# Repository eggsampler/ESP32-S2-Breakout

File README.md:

# ESP32-S2-Breakout

**May 2021:** New v2 boards [assembled with USB-C connector](https://cdn.discordapp.com/attachments/743434443859034135/847350110374461490/image0.jpg), tested and working well over USB CDC-ACM and DFU programming.

**Feb 2021:** Updated to v2, switched from micro usb to usb-c connector, minor routing changes. PCB ordered, updates to come.

**July 2020:** Board has been [assembled](https://i.imgur.com/Ixv2GHa.jpg), but not fully tested. Currently waiting for ESP-IDF release with full s2 support.

This board is a minimal breakout board for the new ESP32-S2-WROOM module from [Espressif](https://www.espressif.com/). It was designed with a few criteria in mind,

- Breakout as many pins as possible, if not all, from the module
- Be relatively easy for a hobbyist to order & assemble
- Use a minimal amount of components

To that end, a few choices were made,

- Designed in [KiCad](https://kicad.org/) to be accessible to most people
- Use as little active components as possible
  - Note, it is definitely possible to use less than is currently laid out and the design will (slowly) be iterated on towards this.
- Using 0603 (imperial) sized passives
  - Ideally the board would be constructed using solder paste, a stencil and either some form of reflow oven or hot plate (even a [skillet on a stove](https://www.sparkfun.com/tutorials/59) is fine)
- To have the boards cheaply manufactured by most turn-key pcb fab houses,
  - Power traces should be at least 12 mil
  - Signal traces should be at least 8 mil
  - Vias should be 0.3mm drill size with a 0.6mm pad size
- No LGA parts, and ideally no QFN parts

## Initial Design

The initial design was taken from the [ESP32-S2-WROOM & ESP32-S2-WROOM-I Datasheet](https://www.espressif.com/sites/default/files/documentation/esp32-s2-wroom_esp32-s2-wroom-i_datasheet_en.pdf) (v0.5) section *6. Peripheral Schematics* Figure 5.

A few changes were made from this schematic.

- The USB data lines were directed to a USB-C connector
- 22 ohm termination resistors are used on the USB data lines, along with including the 20pF caps
- No 0 resistor was used on the EN reset switch, just tied directly to the EN pin
- A switch was also used on IO0 for the boot mode, instead of a connector/header
- No separate connectors for UART/JTAG, all pins were broken out to 2.54mm/0.1" headers

## Component Selection

### 1. 3v3 Regulator

A regulator which has high efficiencies (ie, low ground/quiescent current) is needed to get the best out of powering the device from higher voltages. The XC6220 has a hysterisis mode called "Green Operation" where the supply current current is much lower when the load current is below 2mA. The v1 of this board will also be a bit of a test for this regulator to see how it handles higher loads for wifi, and lower loads for sleep modes.

### 2. 32.768 KHz Crystal

A few resources were useful when researching crystal and component choices.

1. https://en.wikipedia.org/wiki/Pierce_oscillator
2. http://ww1.microchip.com/downloads/en/AppNotes/00943A.pdf
3. http://www.crystek.com/documents/appnotes/Pierce-GateIntroduction.pdf
4. http://www.st.com/internet/com/TECHNICAL_RESOURCES/TECHNICAL_LITERATURE/APPLICATION_NOTE/CD00221665.pdf

A cheap crystal FC-135 with a max ESR of 70kOhms was used which fits on the KiCad 3215 pad. A few passive values will need to be tested for v1 to determine if they're even necessary.

### 3. Switches / Connectors

The switches and connectors were chosen because they had footprints already in the KiCad library and are relatively accessible from most vendors.

### 4. USB ESD Protection

A USBLC6-2SC6 was chosen for ESD protection of the USB power and data lines. This part was already available in KiCad and at a few distributors. An input capacitor was used fort this part, along with a ferrite bead before the 5v bus.

Another ferrite bead and capacitor was used between the shield and the ground. Probably not strictly necessary.

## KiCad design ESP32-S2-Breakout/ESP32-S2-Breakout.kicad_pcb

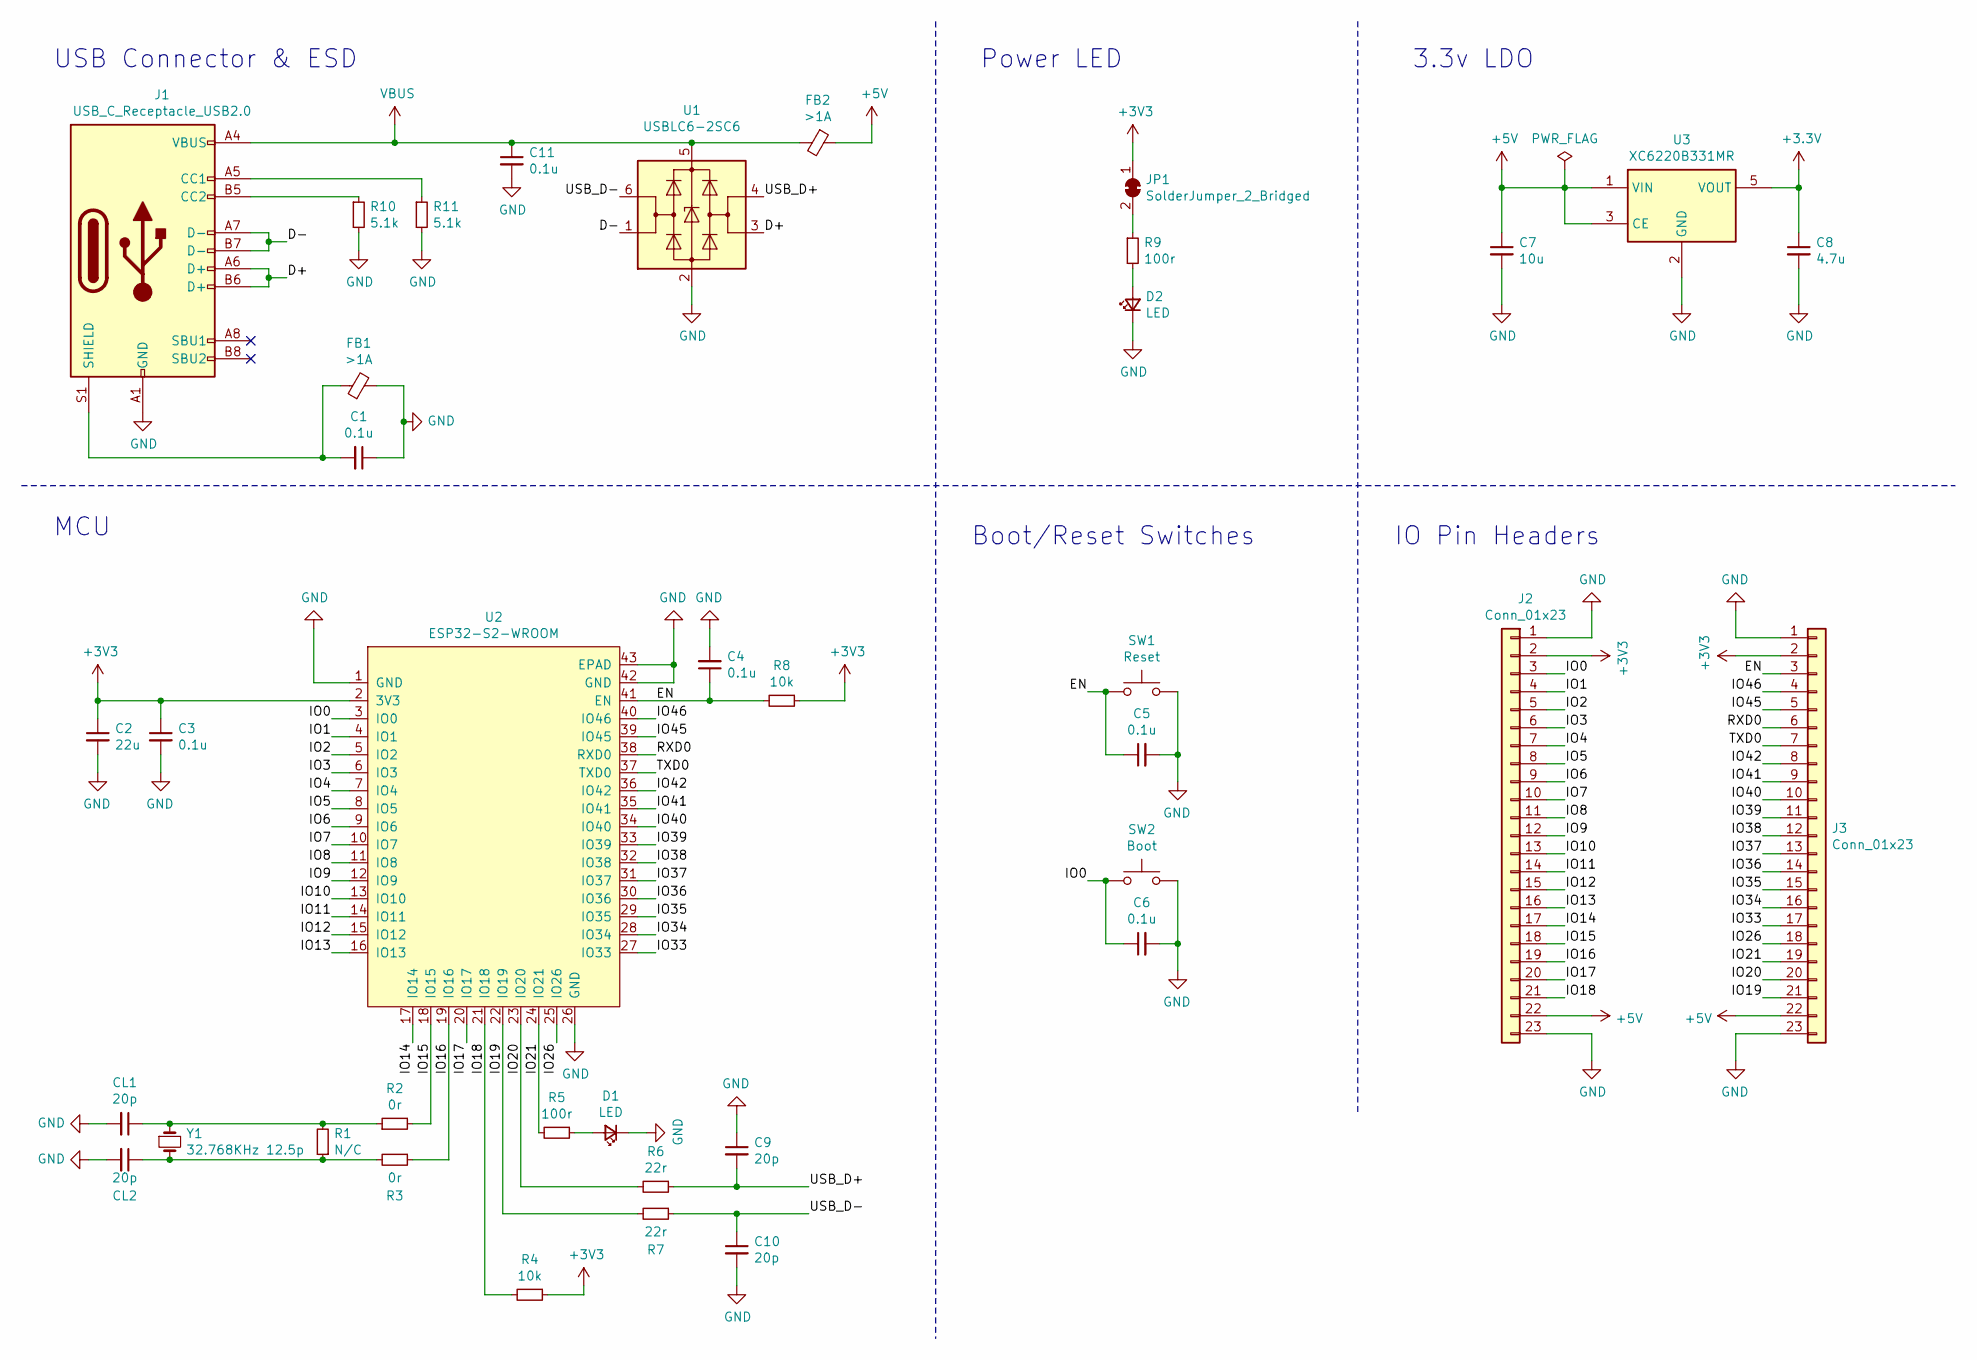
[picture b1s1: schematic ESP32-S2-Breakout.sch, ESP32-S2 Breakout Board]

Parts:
C1, C3, C4, C5, C6, C11: 0.1u; C_0603_1608Metric; LCSC C14663
C2: 22u; C_0603_1608Metric; LCSC C84419
C7: 10u; C_0603_1608Metric; LCSC C90058
C8: 4.7u; C_0603_1608Metric; LCSC C69335
C9, C10: 20p; C_0603_1608Metric; LCSC C1648
CL1, CL2: 20p; C_0603_1608Metric; LCSC C1648
D1: LED; LED_0603_1608Metric; LCSC C205443
D2: LED; LED_0603_1608Metric; LCSC C205445
FB1, FB2: >1A; L_0603_1608Metric; LCSC C24821
J1: USB_C_Receptacle_USB2.0; USB_C_Receptacle_HRO_TYPE-C-31-M-12; LCSC C165948
J2, J3: Conn_01x23; PinHeader_1x23_P2.54mm_Vertical
JP1: SolderJumper_2_Bridged; SolderJumper-2_P1.3mm_Bridged_RoundedPad1.0x1.5mm
R1: N/C; R_0603_1608Metric
R2, R3: 0r; R_0603_1608Metric; LCSC C21189
R4, R8: 10k; R_0603_1608Metric; LCSC C99198
R5, R9: 100r; R_0603_1608Metric; LCSC C22775
R6, R7: 22r; R_0603_1608Metric; LCSC C23345
R10, R11: 5.1k; R_0603_1608Metric; LCSC C163928
SW1: Reset; Alps_SKRK; LCSC C115357
SW2: Boot; Alps_SKRK; LCSC C115357
U1: USBLC6-2SC6; SOT-23-6; LCSC C7519
U2: ESP32-S2-WROOM; LCSC C701327
U3: XC6220B331MR; SOT-23-5; LCSC C86534
Y1: 32.768KHz 12.5p; Crystal_SMD_3215-2Pin_3.2x1.5mm; LCSC C271654

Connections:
+5V: C7.1, FB2.1, J2.22, J3.22, U3.1 (VIN), U3.3 (CE)
/D+: J1.A6 (D+), J1.B6 (D+), U1.3 (I/O2)
/D-: J1.A7 (D-), J1.B7 (D-), U1.1 (I/O1)
/EN: C4.1, C5.1, J3.3, R8.2, SW1.2, U2.41 (EN)
/IO0: C6.1, J2.3, SW2.2, U2.3 (IO0)
/IO1: J2.4, U2.4 (IO1)
/IO2: J2.5, U2.5 (IO2)
/IO3: J2.6, U2.6 (IO3)
/IO4: J2.7, U2.7 (IO4)
/IO5: J2.8, U2.8 (IO5)
/IO6: J2.9, U2.9 (IO6)
/IO7: J2.10, U2.10 (IO7)
/IO8: J2.11, U2.11 (IO8)
/IO9: J2.12, U2.12 (IO9)
/IO10: J2.13, U2.13 (IO10)
/IO11: J2.14, U2.14 (IO11)
/IO12: J2.15, U2.15 (IO12)
/IO13: J2.16, U2.16 (IO13)
/IO14: J2.17, U2.17 (IO14)
/IO15: J2.18, R2.2, U2.18 (IO15)
/IO16: J2.19, R3.1, U2.19 (IO16)
/IO17: J2.20, U2.20 (IO17)
/IO18: J2.21, R4.2, U2.21 (IO18)
/IO19: J3.21, R7.2, U2.22 (IO19)
/IO20: J3.20, R6.2, U2.23 (IO20)
/IO21: J3.19, R5.2, U2.24 (IO21)
/IO26: J3.18, U2.25 (IO26)
/IO33: J3.17, U2.27 (IO33)
/IO34: J3.16, U2.28 (IO34)
/IO35: J3.15, U2.29 (IO35)
/IO36: J3.14, U2.30 (IO36)
/IO37: J3.13, U2.31 (IO37)
/IO38: J3.12, U2.32 (IO38)
/IO39: J3.11, U2.33 (IO39)
/IO40: J3.10, U2.34 (IO40)
/IO41: J3.9, U2.35 (IO41)
/IO42: J3.8, U2.36 (IO42)
/IO45: J3.5, U2.39 (IO45)
/IO46: J3.4, U2.40 (IO46)
/RXD0: J3.6, U2.38 (RXD0)
/TXD0: J3.7, U2.37 (TXD0)
/USB_D+: C9.2, R6.1, U1.4 (I/O2)
/USB_D-: C10.1, R7.1, U1.6 (I/O1)
GND: C1.1, C2.2, C3.2, C4.2, C5.2, C6.2, C7.2, C8.2, C9.1, C10.2, C11.2, CL1.2, CL2.2, D1.1 (K), D2.1 (K), FB1.2, J1.A1 (GND), J1.A12 (GND), J1.B1 (GND), J1.B12 (GND), J2.1, J2.23, J3.1, J3.23, R10.2, R11.2, SW1.1, SW2.1, U1.2 (GND), U2.1 (GND), U2.26 (GND), U2.42 (GND), U2.43 (EPAD), U3.2 (GND)
unnamed: C1.2, FB1.1, J1.S1 (SHIELD)
unnamed: CL1.1, R1.2, R2.1, Y1.1
unnamed: CL2.1, R1.1, R3.2, Y1.2
unnamed: D1.2 (A), R5.1
unnamed: D2.2 (A), R9.2
unnamed: J1.A5 (CC1), R11.1
unnamed: J1.B5 (CC2), R10.1
unnamed: JP1.2 (B), R9.1
VBUS: C11.1, FB2.2, J1.A4 (VBUS), J1.A9 (VBUS), J1.B4 (VBUS), J1.B9 (VBUS), U1.5 (VBUS)

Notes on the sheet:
USB Connector & ESD
Power LED
3.3v LDO
MCU
Boot/Reset Switches
IO Pin Headers

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
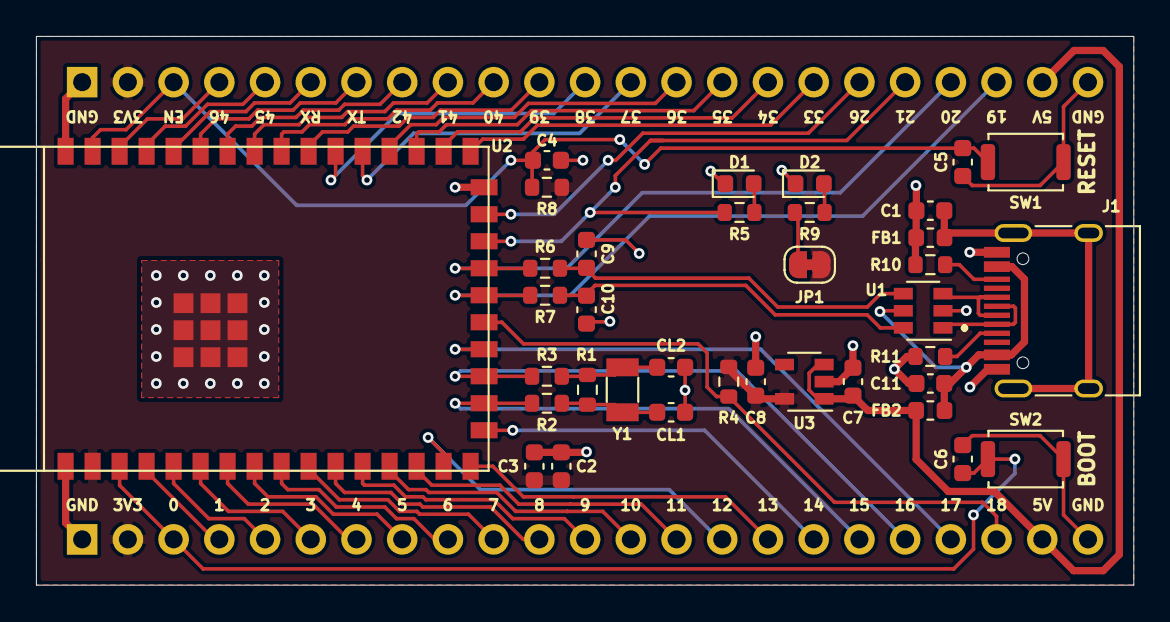
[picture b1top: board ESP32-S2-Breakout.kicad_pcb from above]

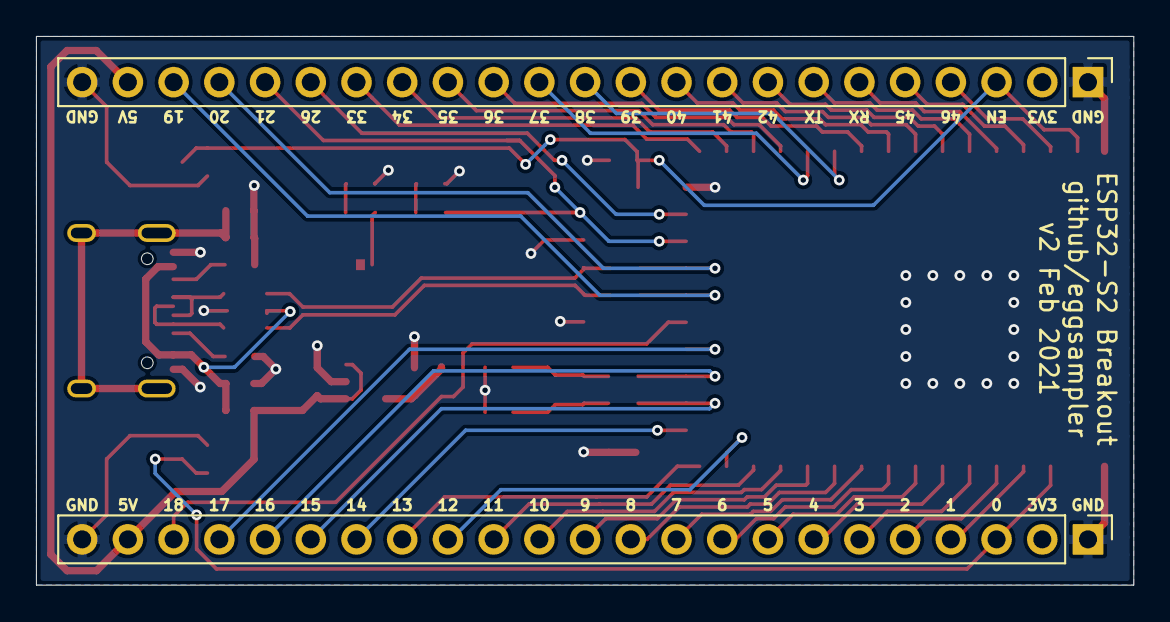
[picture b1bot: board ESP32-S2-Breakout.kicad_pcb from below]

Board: 2 copper layers, 61.0 x 30.5 mm, 38 parts (2 on the bottom side), 54 nets.

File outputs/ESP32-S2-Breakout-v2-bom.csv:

Qty,Reference(s),Value,Footprint,LCSC
6,"C1, C3, C4, C5, C6, C11",0.1u X7R 50V,C_0603_1608Metric,C14663
1,C2,22u X5R 10V,C_0603_1608Metric,C59461
1,C7,10u X5R 16V,C_0603_1608Metric,C19702
1,C8,4.7u X5R 25V,C_0603_1608Metric,C19666
4,"C9, C10, CL1, CL2",20p C0G 50V,C_0603_1608Metric,C1648
1,D1,LED 2.8V 5mA Red,LED_0603_1608Metric,C2286
1,D2,LED 2.8V 5mA Green,LED_0603_1608Metric,C72043
2,"FB1, FB2",>1A,L_0603_1608Metric,C85831
1,J1,USB_C_Receptacle_USB2.0,HRO_TYPE-C-31-M-12,C165948
1,R1,N/C,R_0603_1608Metric,-
2,"R2, R3",0r,R_0603_1608Metric,C21189
2,"R4, R8",10k 5%,R_0603_1608Metric,C25804
2,"R5, R9",100r 1%,R_0603_1608Metric,C22775
2,"R6, R7",22r 1%,R_0603_1608Metric,C23345
2,"R10, R11",5.1k 5%,R_0603_1608Metric,C23186
1,SW1,Reset,Alps_SKRK,C115357
1,SW2,Boot,Alps_SKRK,C115357
1,U1,USBLC6-2SC6,SOT-23-6,C558442
1,U2,ESP32-S2-WROVER,ESP32-S2-WROVER,C701327
1,U3,XC6220B331MR,SOT-23-5,C86534
1,Y1,32.768KHz 12.5pF 70kR,Crystal_SMD_3215,C32346

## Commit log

2020-03-16 Initial hardware commit
2020-03-16 Schematic for v1
2020-03-16 Gerbers for v1
2020-03-16 PCB Images for v1
2020-03-16 Add resistor values for 1.8V/2mA LEDs
2020-03-16 Add USB series termination resistor and bypass capacitor values
2020-03-16 Add resistor and capacitor values for 32.758kHz crystal
2020-03-16 Add values for ferrite bead on usb connector
2020-03-16 Update schematic PDF for new component values
2020-03-16 Update images, add pcb image
2020-03-16 Minor pcb track changes, re-export gerbers and drill files
2020-03-16 Add 5v and extra gnd pin to pin headers, rearrange pcb
2020-03-16 Add v1 gerber zip file
2020-03-17 Added copper pour around EPAD
2020-03-19 Add polarity marker to TVS
2020-03-19 Update gerbers
2020-03-19 Add peripheral schematics image
2020-03-20 Change all passives from 0603 to 0805 Add capacitor to input pin of USBLC6 Update gerbers and images
2020-03-20 Update crystal passive values and readme
2020-07-30 Update README.md
    Add update for assembly and testing
2020-10-19 Update USB TVS
2021-02-07 Rev 2/v2 update
2021-05-27 Minor routing updates, include all updated outputs for v2
2021-05-27 Update README
    Include update for newest v2 board
2021-05-27 Add v2 BOM and centroid file
2021-11-08 Update README.md
    https://forum.kicad.info/t/warning-avoid-all-links-to-kicad-pcb-org-use-kicad-org/31521
